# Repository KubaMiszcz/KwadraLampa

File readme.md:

# KwadraLampa
## TODO:
* rewrite to STM32F103
* communication through wifi - mosquitto and openhab
* redesign PCB for it

## Android App
* ikonka help i about
* ikonka powrot do glownego
* pamietanie ostatniego nadajnika i laczenie automatyczne
* krotkie nazwy nadajnikow
* usun dzwieki na razie bo cos sie krzwayc i za dlugo trwaja nawt po wylaczneiu

## PC Client
* todo

## Arduino firmware
sprawdz czy arduino wysyla co 100ms 10ms przy 9600, jak tak to kombinu z xamarinem:]
ustwiaenia BT i inne do ekranu ustwaienia
komunikacja w obie strony

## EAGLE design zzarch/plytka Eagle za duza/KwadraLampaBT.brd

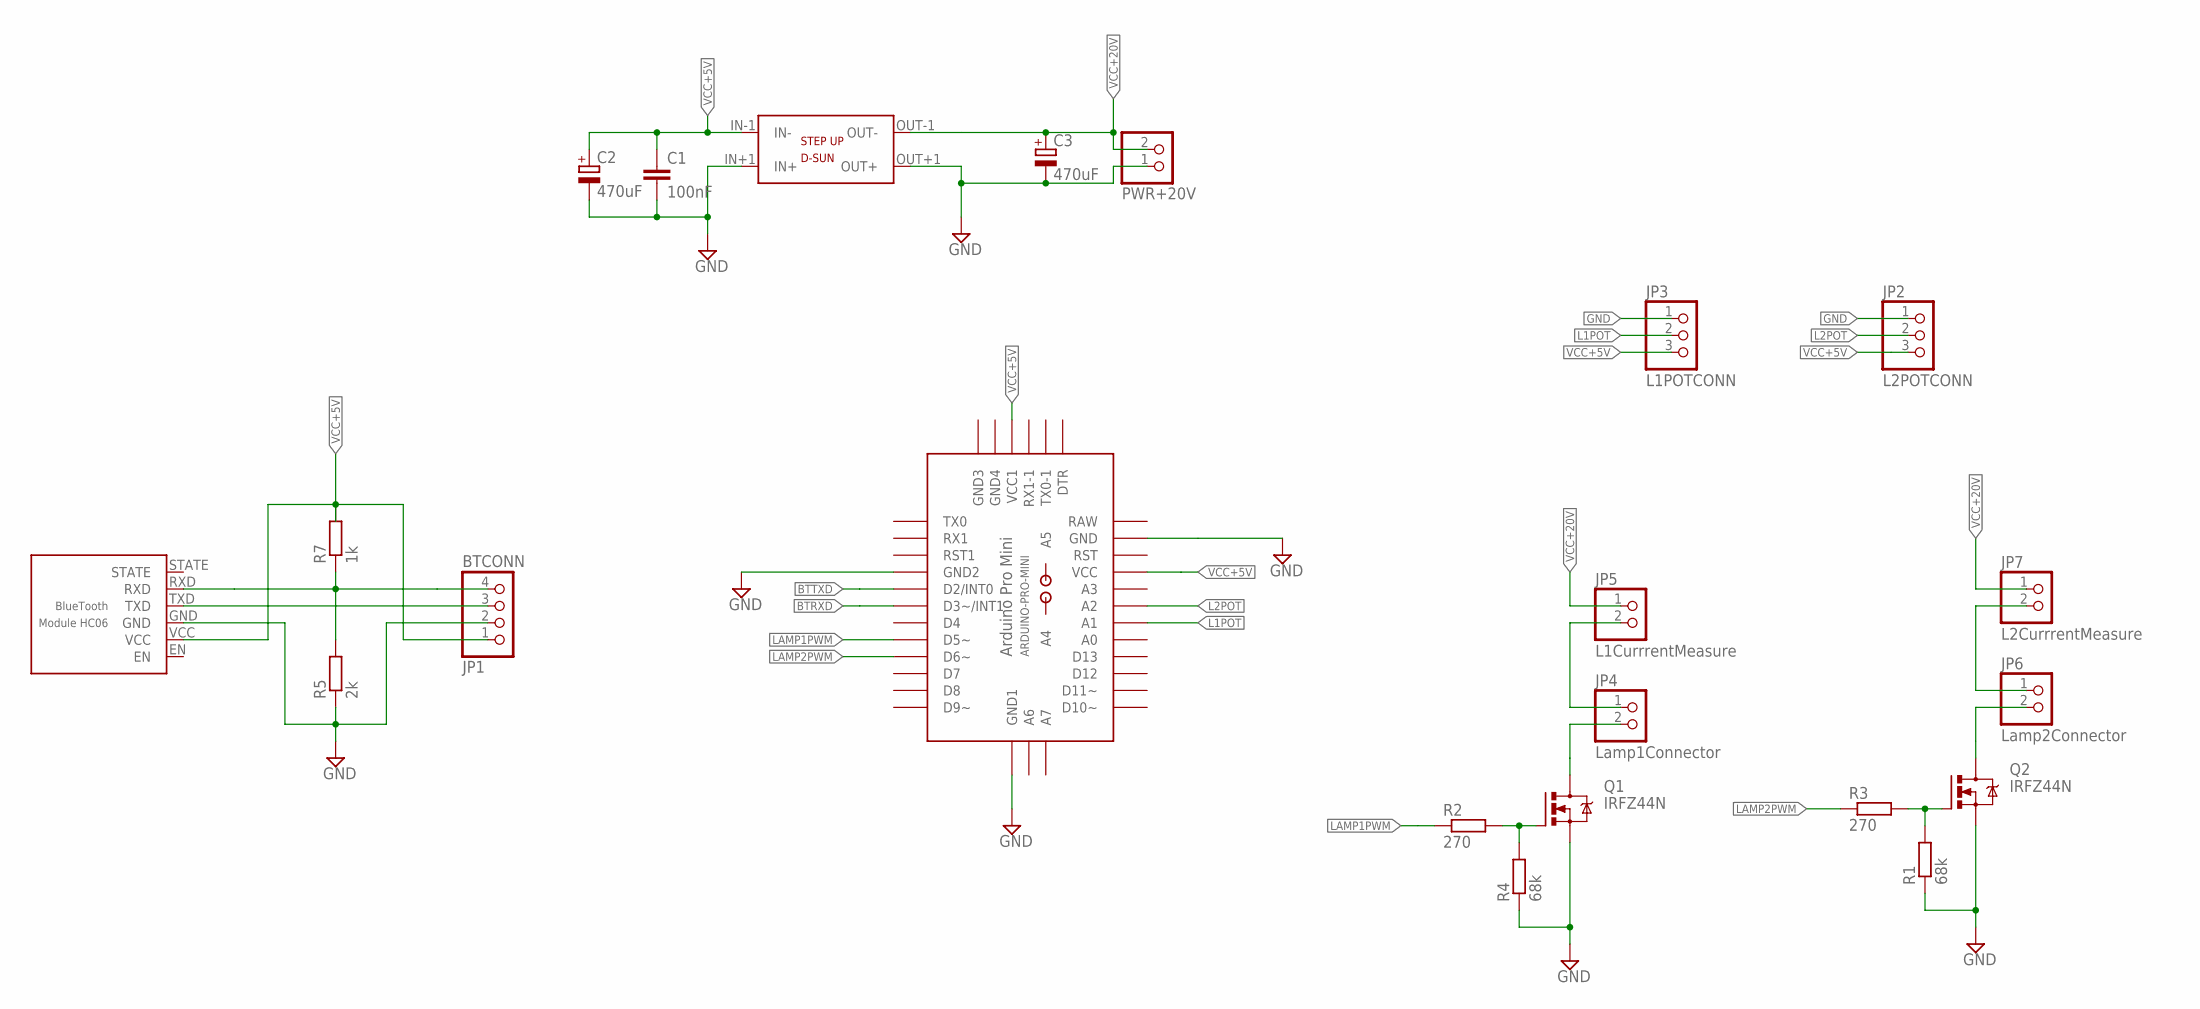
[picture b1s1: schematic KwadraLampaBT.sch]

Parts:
C1: 100nF; C025-025X050
C2, C3: 470uF; C_E_R5-FI13_ELECTROLYTIC
IC1: HC06
JP1: BTCONN; 1X04
JP2: L2POTCONN; 1X03
JP3: L1POTCONN; 1X03
JP4: Lamp1Connector; 1X02
JP5: L1CurrrentMeasure; 1X02
JP6: Lamp2Connector; 1X02
JP7: L2CurrrentMeasure; 1X02
PWR+20V: PINHD-1X2; 1X02
Q1, Q2: IRFZ44N; TO220AB-GDS-VERT
R1, R4: 68k; SMD1206
R2, R3: 270; SMD1206
R5: 2k; SMD1206
R7: 1k; SMD1206
U$1: ARDUINO-PRO-MINI
U$2: STEPUP_D-SUN

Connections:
BTRXD: IC1.RXD, JP1.4, R5.2, R7.1, U$1.D3 (D3~/INT1)
BTTXD: IC1.TXD, JP1.3, U$1.D2 (D2/INT0)
GND: C1.2, C2.-, C3.-, IC1.GND, JP1.2, JP2.1, JP3.1, PWR+20V.1, Q1.S, Q2.S, R1.1, R4.1, R5.1, U$1.GND, U$1.GND1 (GND2), U$1.GND4 (GND1), U$2.IN+1 (IN+), U$2.OUT+1 (OUT+)
L1POT: JP3.2, U$1.A1
L2POT: JP2.2, U$1.A2
LAMP1PWM: R2.1, U$1.D5 (D5~)
LAMP2PWM: R3.1, U$1.D6 (D6~)
unnamed: JP4.2, Q1.D
unnamed: JP6.2, Q2.D
unnamed: Q2.G, R1.2, R3.2
unnamed: Q1.G, R2.2, R4.2
unnamed: JP4.1, JP5.2
unnamed: JP6.1, JP7.2
VCC+5V: C1.1, C2.+, IC1.VCC, JP1.1, JP2.3, JP3.3, R7.2, U$1.VCC, U$1.VCC1, U$2.IN-1 (IN-)
VCC+20V: C3.+, JP5.1, JP7.1, PWR+20V.2, U$2.OUT-1 (OUT-)

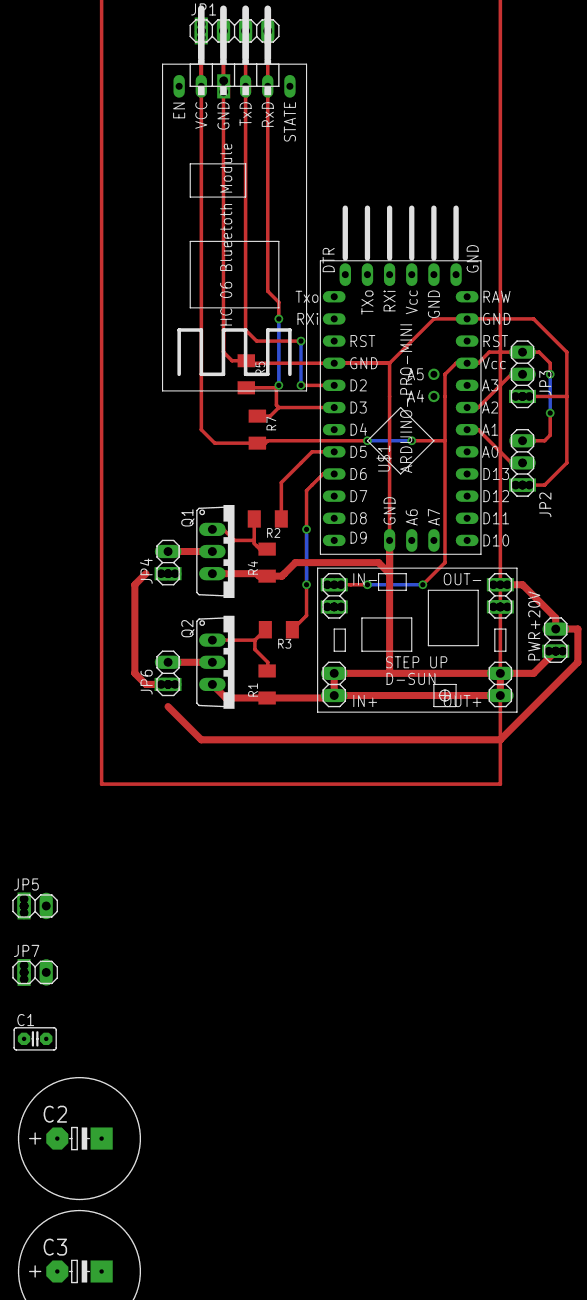
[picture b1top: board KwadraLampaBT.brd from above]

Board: 2 copper layers, 22 parts (0 on the bottom side), 15 nets.

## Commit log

2017-05-17 :lollipop: Added .gitattributes & .gitignore files
